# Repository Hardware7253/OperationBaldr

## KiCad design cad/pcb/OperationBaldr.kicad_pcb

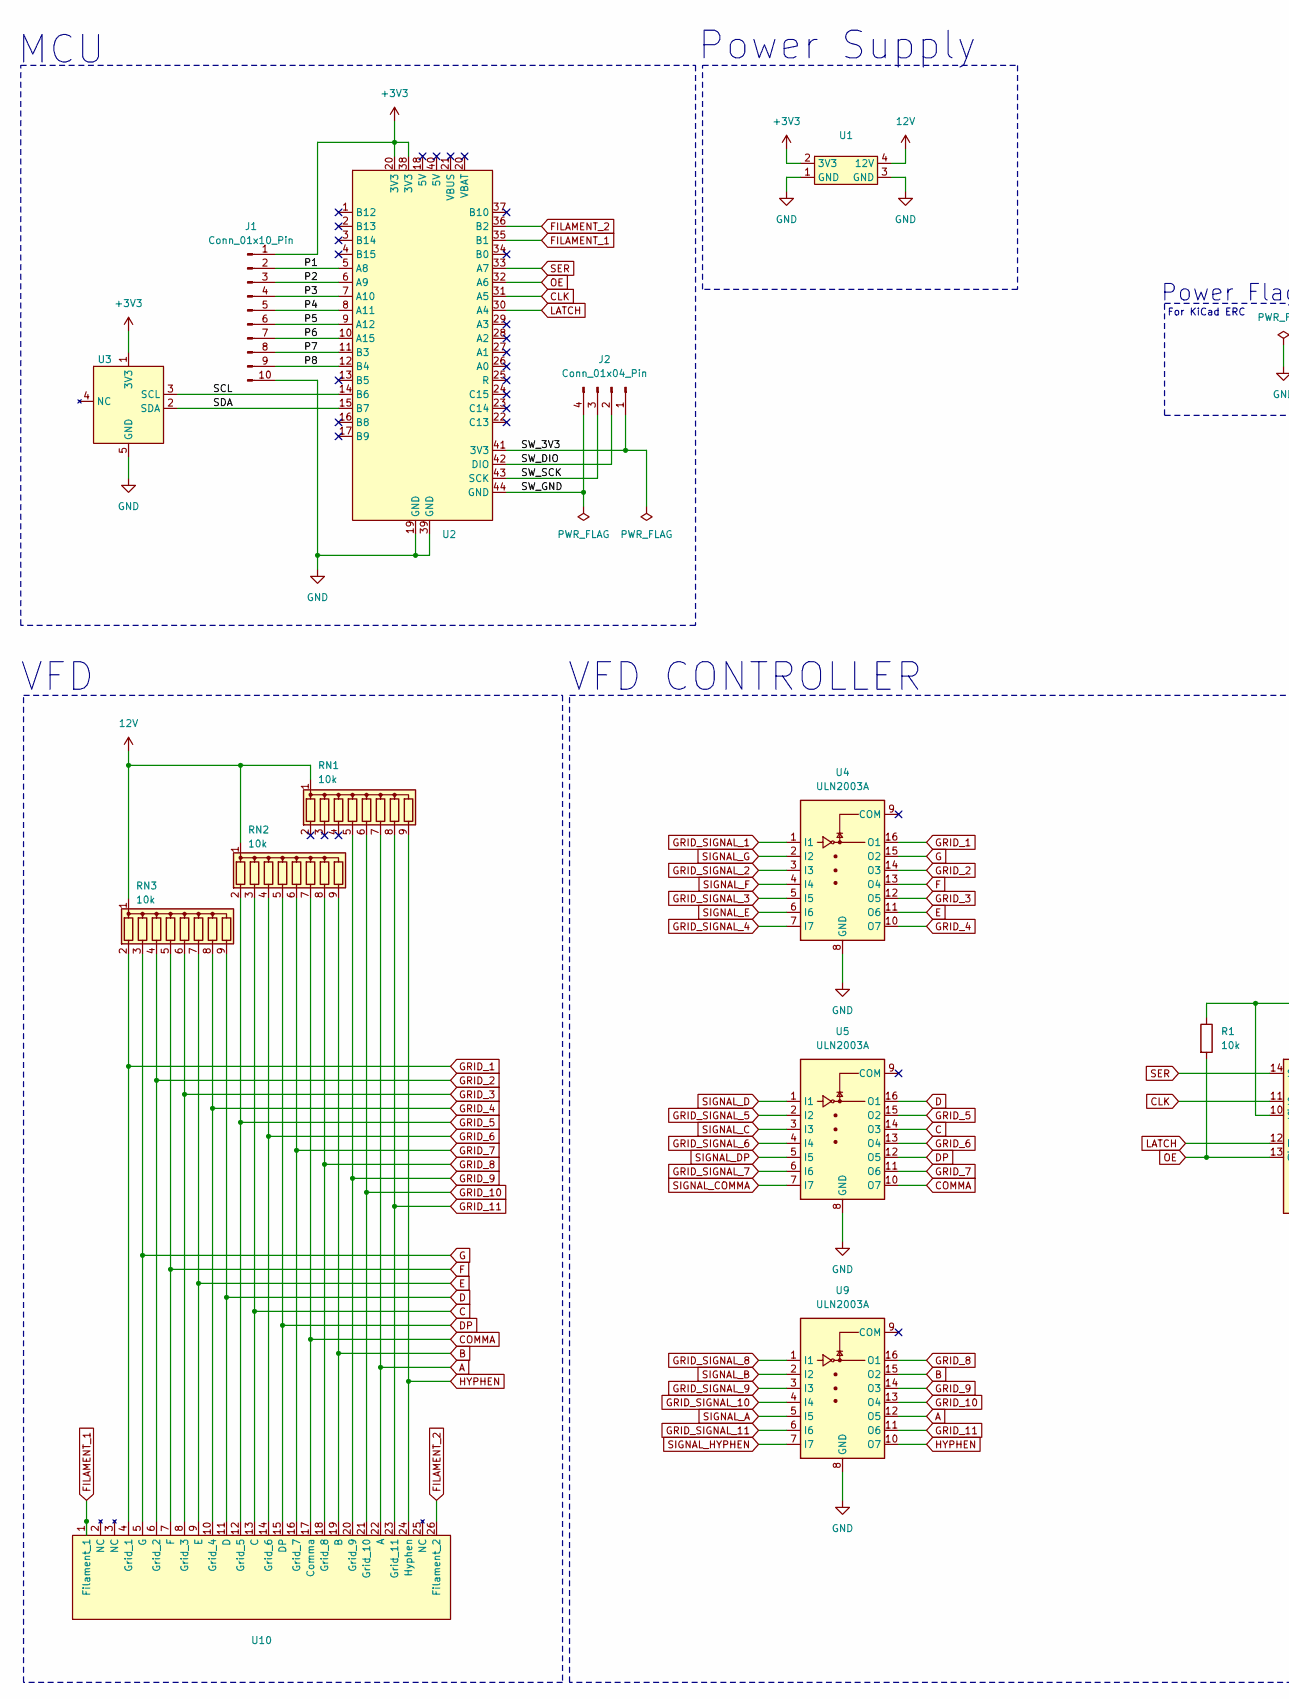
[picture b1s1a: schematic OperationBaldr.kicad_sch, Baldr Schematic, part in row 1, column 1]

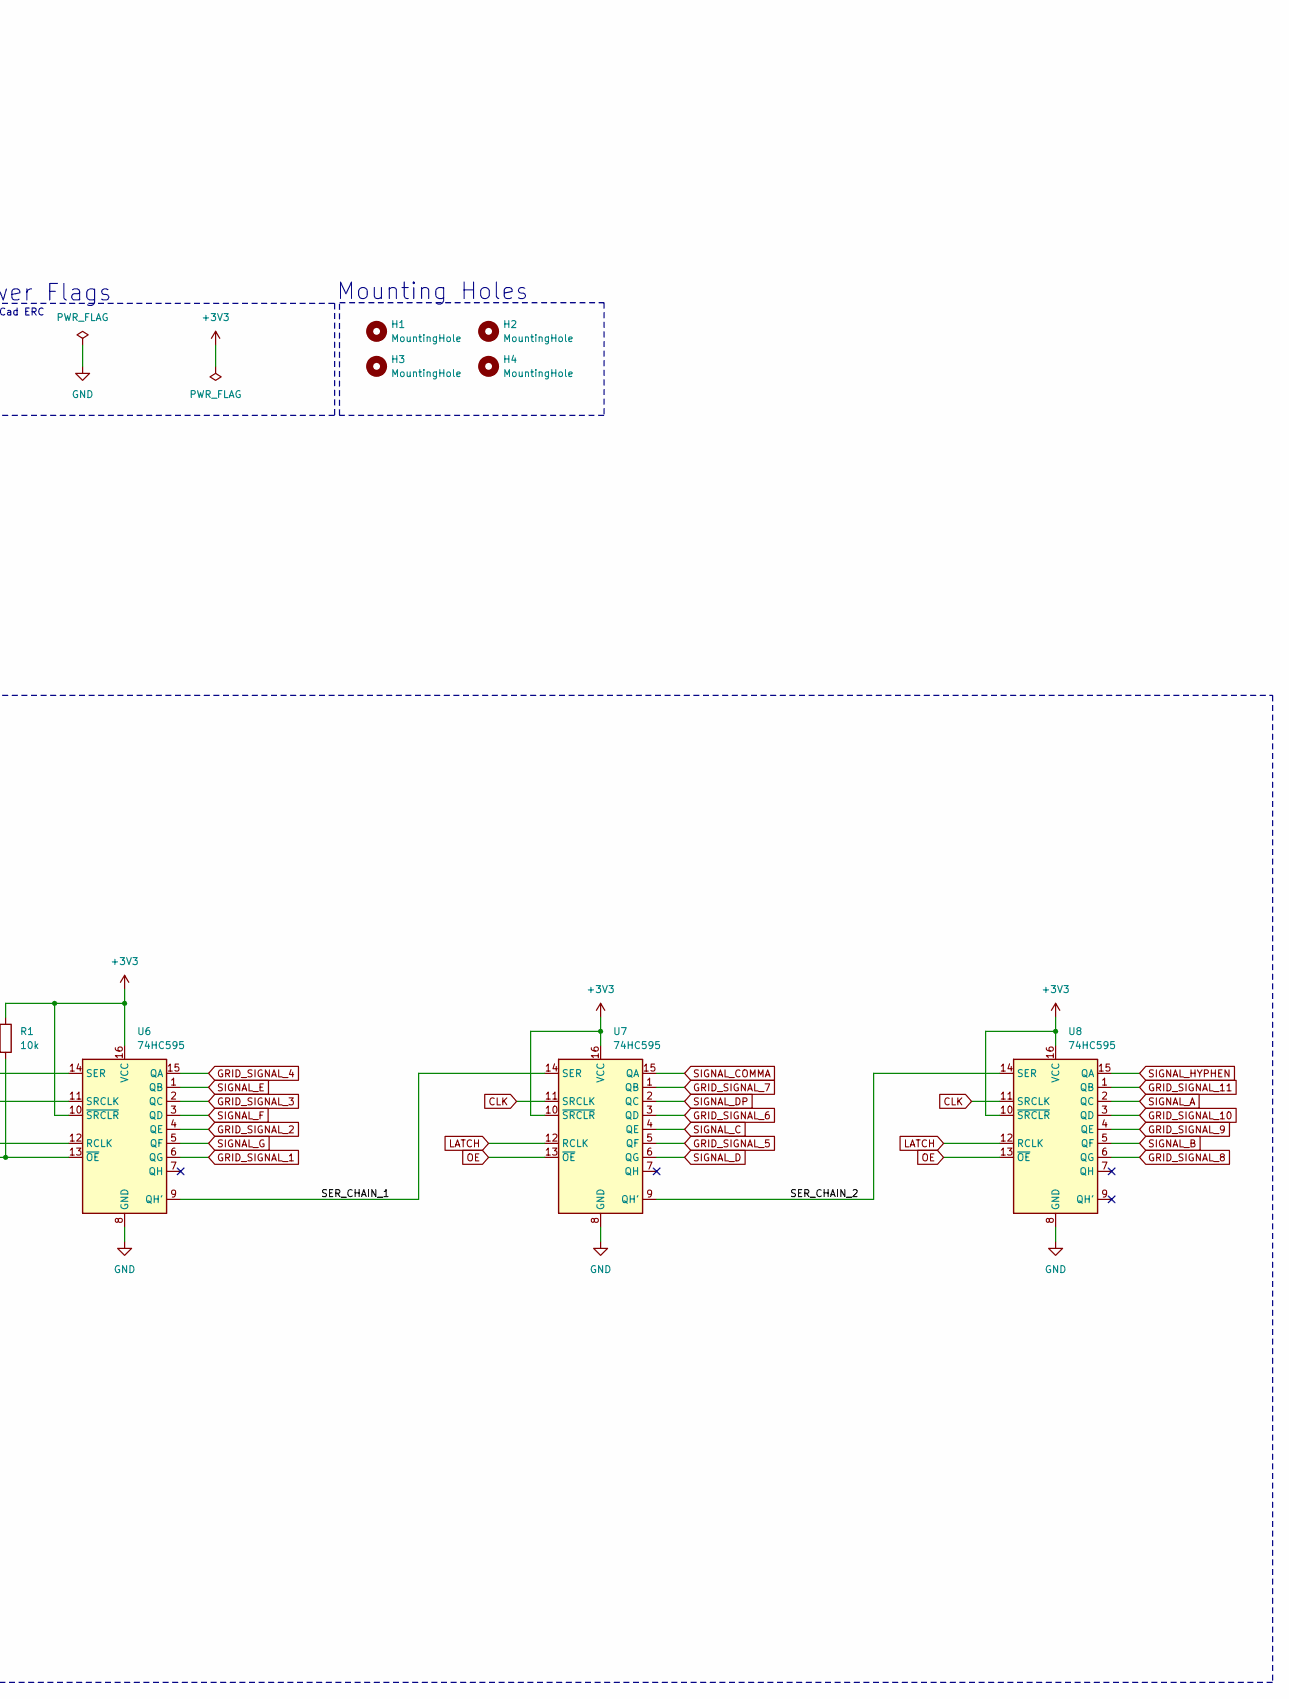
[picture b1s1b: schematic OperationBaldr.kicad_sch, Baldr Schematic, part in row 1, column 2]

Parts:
H1, H2, H3, H4: MountingHole; MountingHole_3.2mm_M3
J1: Conn_01x10_Pin; PinHeader_1x10_P2.54mm_Vertical
J2: Conn_01x04_Pin; PinHeader_1x04_P2.54mm_Horizontal
R1: 10k; R_Axial_DIN0207_L6.3mm_D2.5mm_P10.16mm_Horizontal
RN1, RN2, RN3: 10k; R_Array_SIP9
U1: DC_step_up
U2: STM32_blackpill
U3: RTC
U4, U5, U9: ULN2003A; DIP-16_W7.62mm_Socket
U6, U7, U8: 74HC595; DIP-16_W7.62mm_Socket
U10: ZD1880

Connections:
12V: RN1.1 (common), RN2.1 (common), RN3.1 (common), U1.4 (12V)
+3V3: J1.1, R1.1, U1.2 (3V3), U2.20 (3V3), U2.38 (3V3), U3.1 (3V3), U6.10 (~SRCLR), U6.16 (VCC), U7.10 (~SRCLR), U7.16 (VCC), U8.10 (~SRCLR), U8.16 (VCC)
/P1: J1.2, U2.5 (A8)
/P2: J1.3, U2.6 (A9)
/P3: J1.4, U2.7 (A10)
/P4: J1.5, U2.8 (A11)
/P5: J1.6, U2.9 (A12)
/P6: J1.7, U2.10 (A15)
/P7: J1.8, U2.11 (B3)
/P8: J1.9, U2.12 (B4)
/SCL: U2.14 (B6), U3.3 (SCL)
/SDA: U2.15 (B7), U3.2 (SDA)
/SER_CHAIN_1: U6.9 (QH'), U7.14 (SER)
/SER_CHAIN_2: U7.9 (QH'), U8.14 (SER)
/SW_3V3: J2.1, U2.41 (3V3)
/SW_DIO: J2.2, U2.42 (DIO)
/SW_GND: J2.4, U2.44 (GND)
/SW_SCK: J2.3, U2.43 (SCK)
A: RN1.7 (R6), U9.12 (O5), U10.22 (A)
B: RN2.9 (R8), U9.15 (O2), U10.19 (B)
C: RN2.3 (R2), U5.14 (O3), U10.13 (C)
CLK: U2.31 (A5), U6.11 (SRCLK), U7.11 (SRCLK), U8.11 (SRCLK)
COMMA: RN2.7 (R6), U5.10 (O7), U10.17 (Comma)
D: RN3.9 (R8), U5.16 (O1), U10.11 (D)
DP: RN2.5 (R4), U5.12 (O5), U10.15 (DP)
E: RN3.7 (R6), U4.11 (O6), U10.9 (E)
F: RN3.5 (R4), U4.13 (O4), U10.7 (F)
FILAMENT_1: U2.35 (B1), U10.1 (Filament_1)
FILAMENT_2: U2.36 (B2), U10.26 (Filament_2)
G: RN3.3 (R2), U4.15 (O2), U10.5 (G)
GND: J1.10, U1.1 (GND), U1.3 (GND), U2.19 (GND), U2.39 (GND), U3.5 (GND), U4.8 (GND), U5.8 (GND), U6.8 (GND), U7.8 (GND), U8.8 (GND), U9.8 (GND)
GRID_1: RN3.2 (R1), U4.16 (O1), U10.4 (Grid_1)
GRID_2: RN3.4 (R3), U4.14 (O3), U10.6 (Grid_2)
GRID_3: RN3.6 (R5), U4.12 (O5), U10.8 (Grid_3)
GRID_4: RN3.8 (R7), U4.10 (O7), U10.10 (Grid_4)
GRID_5: RN2.2 (R1), U5.15 (O2), U10.12 (Grid_5)
GRID_6: RN2.4 (R3), U5.13 (O4), U10.14 (Grid_6)
GRID_7: RN2.6 (R5), U5.11 (O6), U10.16 (Grid_7)
GRID_8: RN2.8 (R7), U9.16 (O1), U10.18 (Grid_8)
GRID_9: RN1.5 (R4), U9.14 (O3), U10.20 (Grid_9)
GRID_10: RN1.6 (R5), U9.13 (O4), U10.21 (Grid_10)
GRID_11: RN1.8 (R7), U9.11 (O6), U10.23 (Grid_11)
GRID_SIGNAL_1: U4.1 (I1), U6.6 (QG)
GRID_SIGNAL_2: U4.3 (I3), U6.4 (QE)
GRID_SIGNAL_3: U4.5 (I5), U6.2 (QC)
GRID_SIGNAL_4: U4.7 (I7), U6.15 (QA)
GRID_SIGNAL_5: U5.2 (I2), U7.5 (QF)
GRID_SIGNAL_6: U5.4 (I4), U7.3 (QD)
GRID_SIGNAL_7: U5.6 (I6), U7.1 (QB)
GRID_SIGNAL_8: U8.6 (QG), U9.1 (I1)
GRID_SIGNAL_9: U8.4 (QE), U9.3 (I3)
GRID_SIGNAL_10: U8.3 (QD), U9.4 (I4)
GRID_SIGNAL_11: U8.1 (QB), U9.6 (I6)
HYPHEN: RN1.9 (R8), U9.10 (O7), U10.24 (Hyphen)
LATCH: U2.30 (A4), U6.12 (RCLK), U7.12 (RCLK), U8.12 (RCLK)
OE: R1.2, U2.32 (A6), U6.13 (~OE), U7.13 (~OE), U8.13 (~OE)
SER: U2.33 (A7), U6.14 (SER)
SIGNAL_A: U8.2 (QC), U9.5 (I5)
SIGNAL_B: U8.5 (QF), U9.2 (I2)
SIGNAL_C: U5.3 (I3), U7.4 (QE)
SIGNAL_COMMA: U5.7 (I7), U7.15 (QA)
SIGNAL_D: U5.1 (I1), U7.6 (QG)
SIGNAL_DP: U5.5 (I5), U7.2 (QC)
SIGNAL_E: U4.6 (I6), U6.1 (QB)
SIGNAL_F: U4.4 (I4), U6.3 (QD)
SIGNAL_G: U4.2 (I2), U6.5 (QF)
SIGNAL_HYPHEN: U8.15 (QA), U9.7 (I7)

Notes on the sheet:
For KiCad ERC
VFD CONTROLLER
Mounting Holes
Power Flags
VFD
MCU
Power Supply

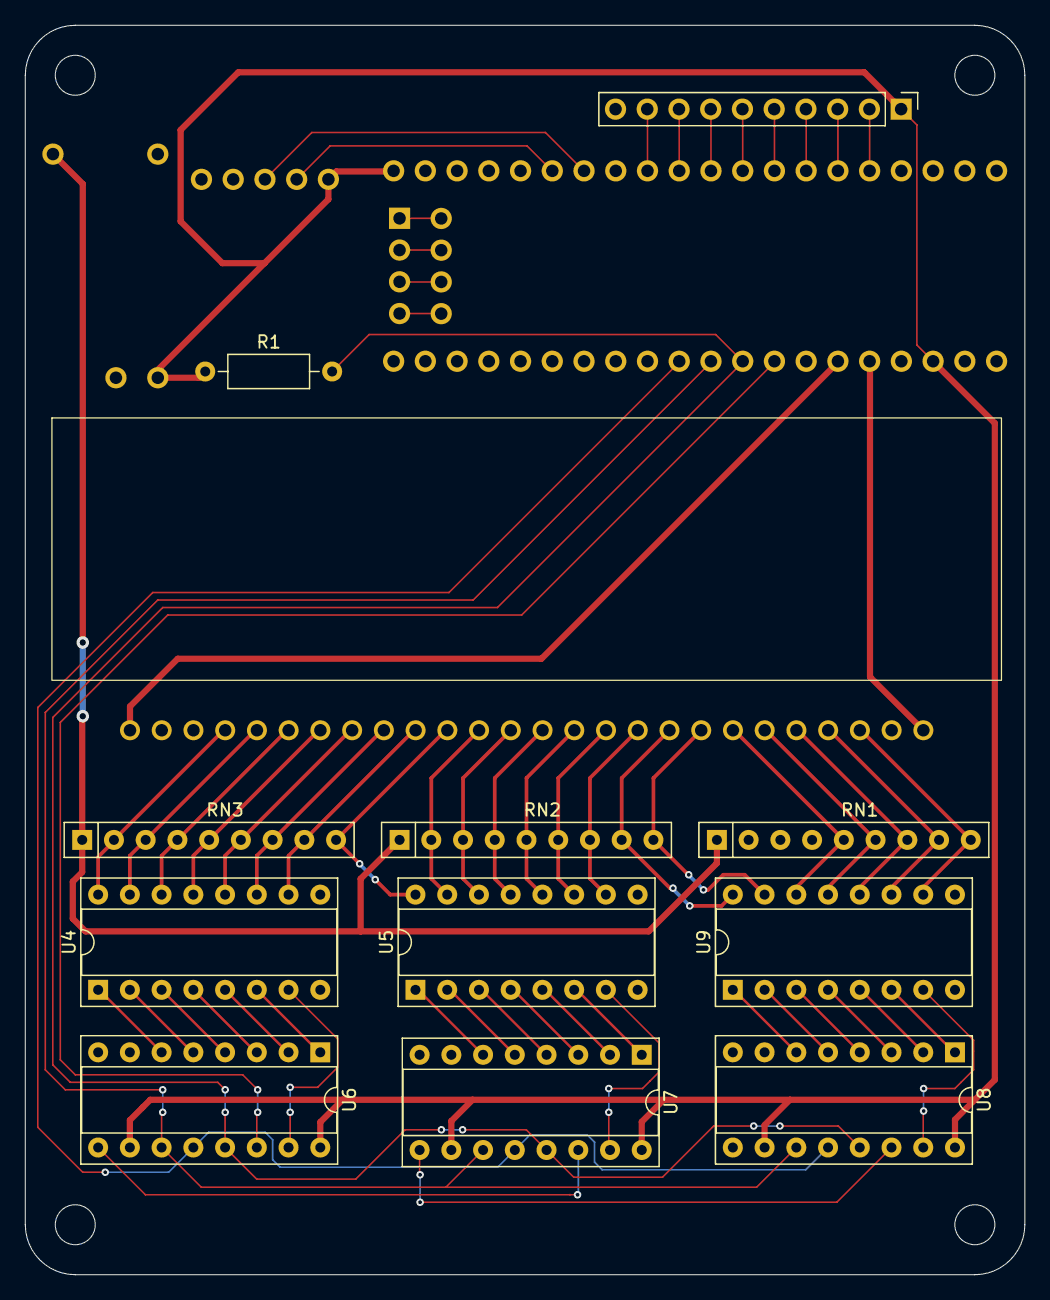
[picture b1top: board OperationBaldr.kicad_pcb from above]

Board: 2 copper layers, 80.0 x 100.0 mm, 20 parts (1 on the bottom side), 67 nets.

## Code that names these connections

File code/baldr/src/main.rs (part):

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    filament_timer.listen(timer::Event::Update);

    // Obtain filament pin handles, and intialise them so that there is a potential difference accross the filament wires
    let mut filament_1 = gpiob.pb2.into_push_pull_output();
    let mut filament_2 = gpiob.pb1.into_push_pull_output();
    filament_1.set_high();
    filament_2.set_low();

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
    let mut vfd = vfd::Vfd {
        spi_bus: Spi::new(dp.SPI1, spi_pins, spi_mode, 100.kHz(), &clocks),
        latch_pin: gpioa.pa4.into_push_pull_output(),
        oe_pin: gpioa.pa6.into_open_drain_output(),
    };

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
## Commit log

2024-06-19 updated gerbers
2024-07-05 Added cad directory
    Added cad directory with casing step file. Also made a minor
    schematic revision (adding values to the resistor networks).
2024-08-28 Added embedded rust code
    Added an embedded rust program to control the device.
    Also restructered file hierarchy, and made revisions to schematic/pcb.
2024-10-01 Changed button pins
    Changed button pins to avoid using the USB and SWD pins
